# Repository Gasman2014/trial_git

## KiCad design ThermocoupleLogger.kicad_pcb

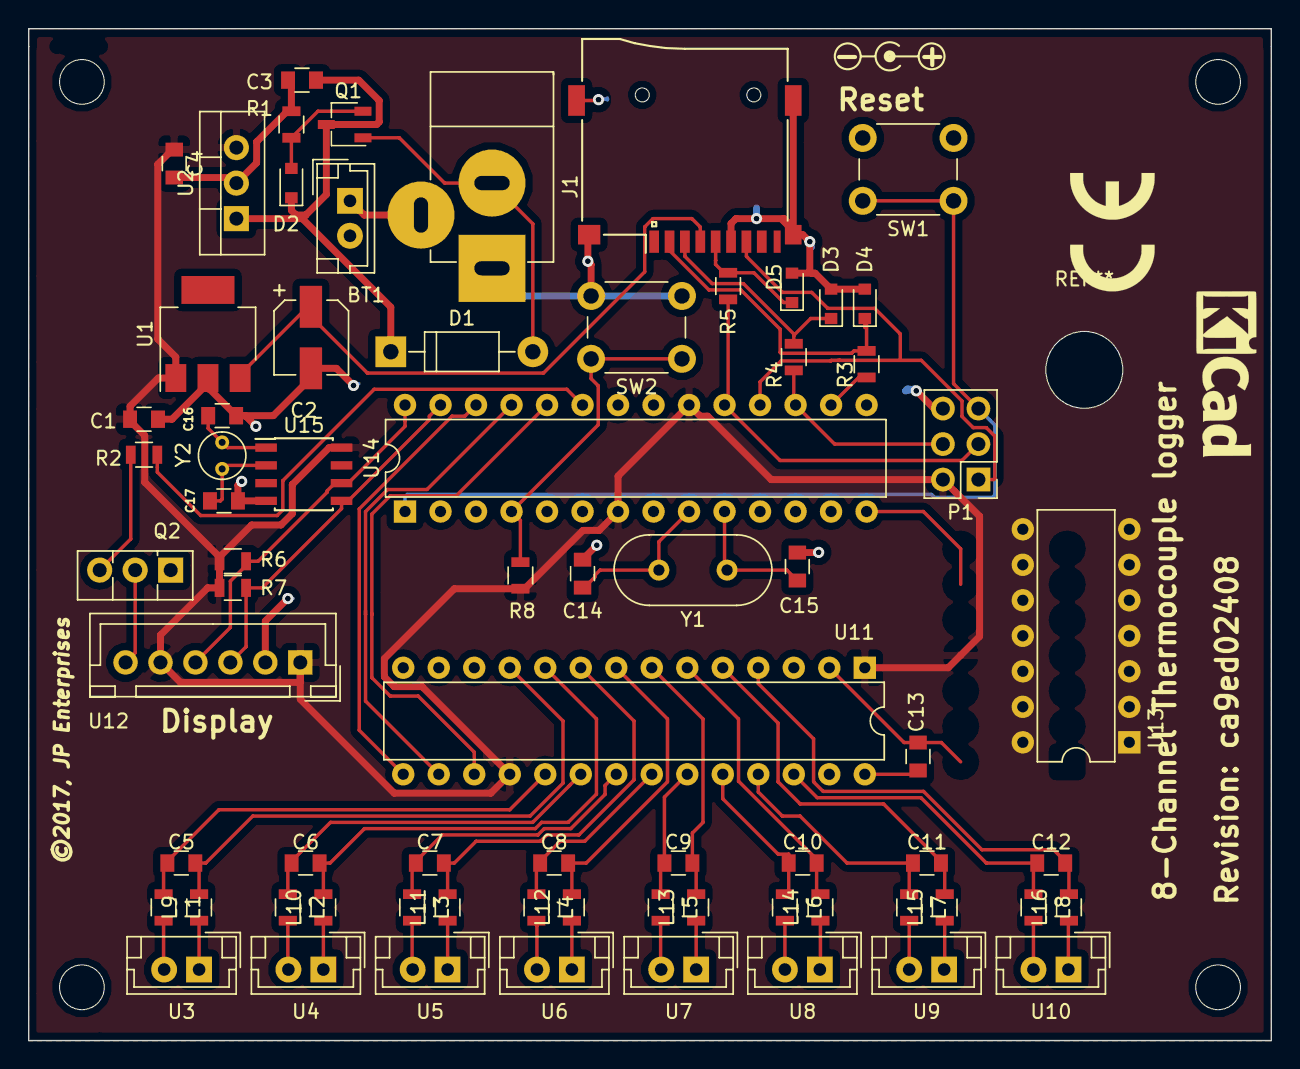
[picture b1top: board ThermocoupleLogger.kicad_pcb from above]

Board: 2 copper layers, 88.9 x 72.4 mm, 74 parts (0 on the bottom side), 62 nets.

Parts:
BT1: 9V; JST_EH_B02B-EH-A_02x2.50mm_Straight
C1: 0.47uF; C_0805
C2: 33uF; CP_Elec_5x5.3
C3: 0.33uF; C_0805
C4: 0.1uF; C_0805
C5, C6, C7, C8, C9, C10, C11, C12, C13: 10nF; C_0805
C14, C15: 18pF; C_0805
C16, C17: 12.5pF; C_0805
D1: 1N4007; D_DO-41_SOD81_P10.16mm_Horizontal
D2: 9V; D_0805
D3, D4, D5: 3.3V; D_0805
J1: Barrel_Jack; JACK_ALIM
L1, L2, L3, L4, L5, L6, L7, L8, L9, L10, L11, L12, L13, L14, L15, L16: 150Ω; L_0805
P1: CONN_02X03; Pin_Header_Straight_2x03_Pitch2.54mm
Q1: BS250; TSOT-23
Q2: BD139; TO-126_Vertical
R1: DNP; R_0805
R2, R8: 10K; R_0805
R3, R4, R5: 220Ω; R_0805
R6, R7: 4.7k; R_0805
REF02, REF03, REF04: MountingHole_3.2mm_M3
SW1, SW2: SW_Push; SW_PUSH_6mm_h5mm
U1: LM3940; SOT-223
U2: 7805; TO-220_Vertical
U3, U4, U5, U6, U7, U8, U9, U10: TC_Connector; JST_EH_B02B-EH-A_02x2.50mm_Straight
U11: ADG407; DIP-28_W7.62mm
U12: I2C_20x4_DISPLAY; JST_XH_B06B-XH-A_06x2.50mm_Straight
U13: AD595; DIP-14_W7.62mm
U14: ATMEGA328P-PU; DIP-28_W7.62mm
U15: DS1307+; SOIC-8_3.9x4.9mm_Pitch1.27mm
XS1: SD_ebay-uSD-push/push_SMD; Conn_uSDcard
Y1: 16MHz; Crystal_HC49-U_Vertical
Y2: 32.768kHz; Crystal_Round_d3.0mm_Vertical

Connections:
3V3: C2.1, U1.3, XS1.4
5V0: C1.1, C4.1, P1.2, R6.1, R7.1, R8.1, U1.1, U2.3, U11.1, U11.18, U12.1, U12.5, U13.11, U14.7, U14.20, U15.8
9V0: C3.1, D1.1, D2.1, Q1.3, U2.1
/Thermocouple connectors/SA1: C5.1, L1.1, U11.19
/Thermocouple connectors/SA2: C6.1, L2.1, U11.20
/Thermocouple connectors/SA3: C7.1, L3.1, U11.21
/Thermocouple connectors/SA4: C8.1, L4.1, U11.22
/Thermocouple connectors/SA5: C9.1, L5.1, U11.23
/Thermocouple connectors/SA6: C10.1, L6.1, U11.24
/Thermocouple connectors/SA7: C11.1, L7.1, U11.25
/Thermocouple connectors/SA8: C12.1, L8.1, U11.26
/Thermocouple connectors/SB1: C5.2, L9.2, U11.11
/Thermocouple connectors/SB2: C6.2, L10.2, U11.10
/Thermocouple connectors/SB3: C7.2, L11.2, U11.9
/Thermocouple connectors/SB4: C8.2, L12.2, U11.8
/Thermocouple connectors/SB5: C9.2, L13.2, U11.7
/Thermocouple connectors/SB6: C10.2, L14.2, U11.6
/Thermocouple connectors/SB7: C11.2, L15.2, U11.5
/Thermocouple connectors/SB8: C12.2, L16.2, U11.4
B_LIGHT: R2.1, U14.23
DB_MUX: C13.2, U11.2, U13.14
GND: BT1.2, C1.2, C2.2, C3.2, C4.2, C13.1, C14.1, C15.1, C16.2, C17.2, D3.2, D4.2, D5.2, J1.1, P1.6, Q2.1, R1.2, SW1.2, SW2.2, U1.2, U2.2, U11.12, U11.28, U12.2, U13.1, U13.4, U13.7, U13.13, U14.8, U14.22, U15.4, XS1.6
MISO: P1.1, U14.18, XS1.7
MOSI: P1.4, R4.1, U14.17
unnamed: BT1.1, J1.3
unnamed: C14.2, U14.9, Y1.2
unnamed: C15.2, U14.10, Y1.1
unnamed: C16.1, U15.1, Y2.1
unnamed: C17.1, U15.2, Y2.2
unnamed: D1.2, J1.2, Q1.1
unnamed: D2.2, Q1.2, R1.1
unnamed: D3.1, R4.2, XS1.3
unnamed: D4.1, R3.2, XS1.2
unnamed: D5.1, R5.2, XS1.5
unnamed: L1.2, U3.2
unnamed: L2.2, U4.2
unnamed: L3.2, U5.2
unnamed: L4.2, U6.2
unnamed: L5.2, U7.2
unnamed: L6.2, U8.2
unnamed: L7.2, U9.2
unnamed: L8.2, U10.2
unnamed: L9.1, U3.1
unnamed: L10.1, U4.1
unnamed: L11.1, U5.1
unnamed: L12.1, U6.1
unnamed: L13.1, U7.1
unnamed: L14.1, U8.1
unnamed: L15.1, U9.1
unnamed: L16.1, U10.1
unnamed: Q2.2, U12.6
unnamed: Q2.3, R2.2
unnamed: R8.2, SW2.1, U14.4
RESET: P1.5, SW1.1, U14.1
SCK: P1.3, R5.1, U14.19
SCL: R6.2, U12.4, U14.28, U15.6
SDA: R7.2, U12.3, U14.27, U15.5
SLCT0: U11.17, U14.24
SLCT1: U11.16, U14.25
SLCT2: U11.15, U14.26
SS: R3.1, U14.16
TEMP: U13.8, U13.9, U14.14

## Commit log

2017-08-02 Commit2
2017-08-02 Amend3
2017-08-14 Test edits
2017-12-17 Add GOO.py - test python git list
2017-12-17 Add GOO.py - add another random commit message
2017-12-19 Random message
2017-12-19 Another andom messages
2017-12-21 Frames v1
2017-12-28 Add Gu5 with landscape orientation of commit windows
2017-12-28 Minor edit to striping logic
2018-07-25 Add test junk
2020-03-17 Adjusted resources
2020-03-17 Reconnect MCU pins
2020-03-17 Reconnect TC amplifier
2020-03-17 Reconnect RTC
2020-03-17 Removed unescessary sheet
2021-01-05 Random edit
2023-01-16 zero

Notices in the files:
ThermocoupleLogger.kicad_pcb:
©2017, JP Enterprises
